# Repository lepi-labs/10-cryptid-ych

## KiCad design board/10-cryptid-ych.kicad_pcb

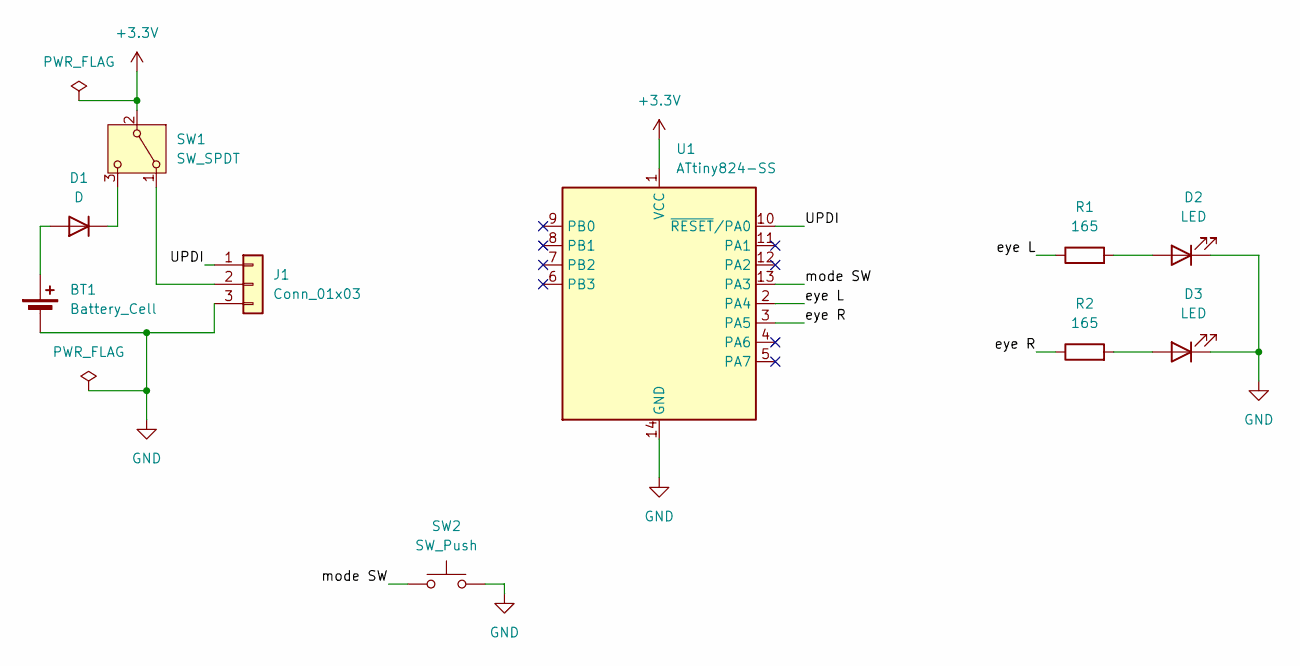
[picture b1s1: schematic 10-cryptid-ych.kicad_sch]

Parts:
BT1: Battery_Cell; BATHLD003SMT
D1: D; D_1206_3216Metric_Pad1.42x1.75mm_HandSolder
D2, D3: LED; LTSTS110KGKT
J1: Conn_01x03; Connector_UPDI_Pad
R1, R2: 165; R_1206_3216Metric_Pad1.30x1.75mm_HandSolder
SW1: SW_SPDT; SWS010020R12SSA
SW2: SW_Push; PHAP3344CR
U1: ATtiny824-SS; SOIC-14_3.9x8.7mm_P1.27mm

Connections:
+3.3V: SW1.2 (B), U1.1 (VCC)
/UPDI: J1.1, U1.10 (~RESET/PA0)
/eye L: R1.1, U1.2 (PA4)
/eye R: R2.1, U1.3 (PA5)
/mode SW: SW2.1, U1.13 (PA3)
GND: BT1.2 (-), D2.1 (K), D3.1 (K), J1.3, SW2.2, U1.14 (GND)
unnamed: BT1.1 (+), D1.2 (A)
unnamed: D1.1 (K), SW1.3 (C)
unnamed: D2.2 (A), R1.2
unnamed: D3.2 (A), R2.2
unnamed: J1.2, SW1.1 (A)

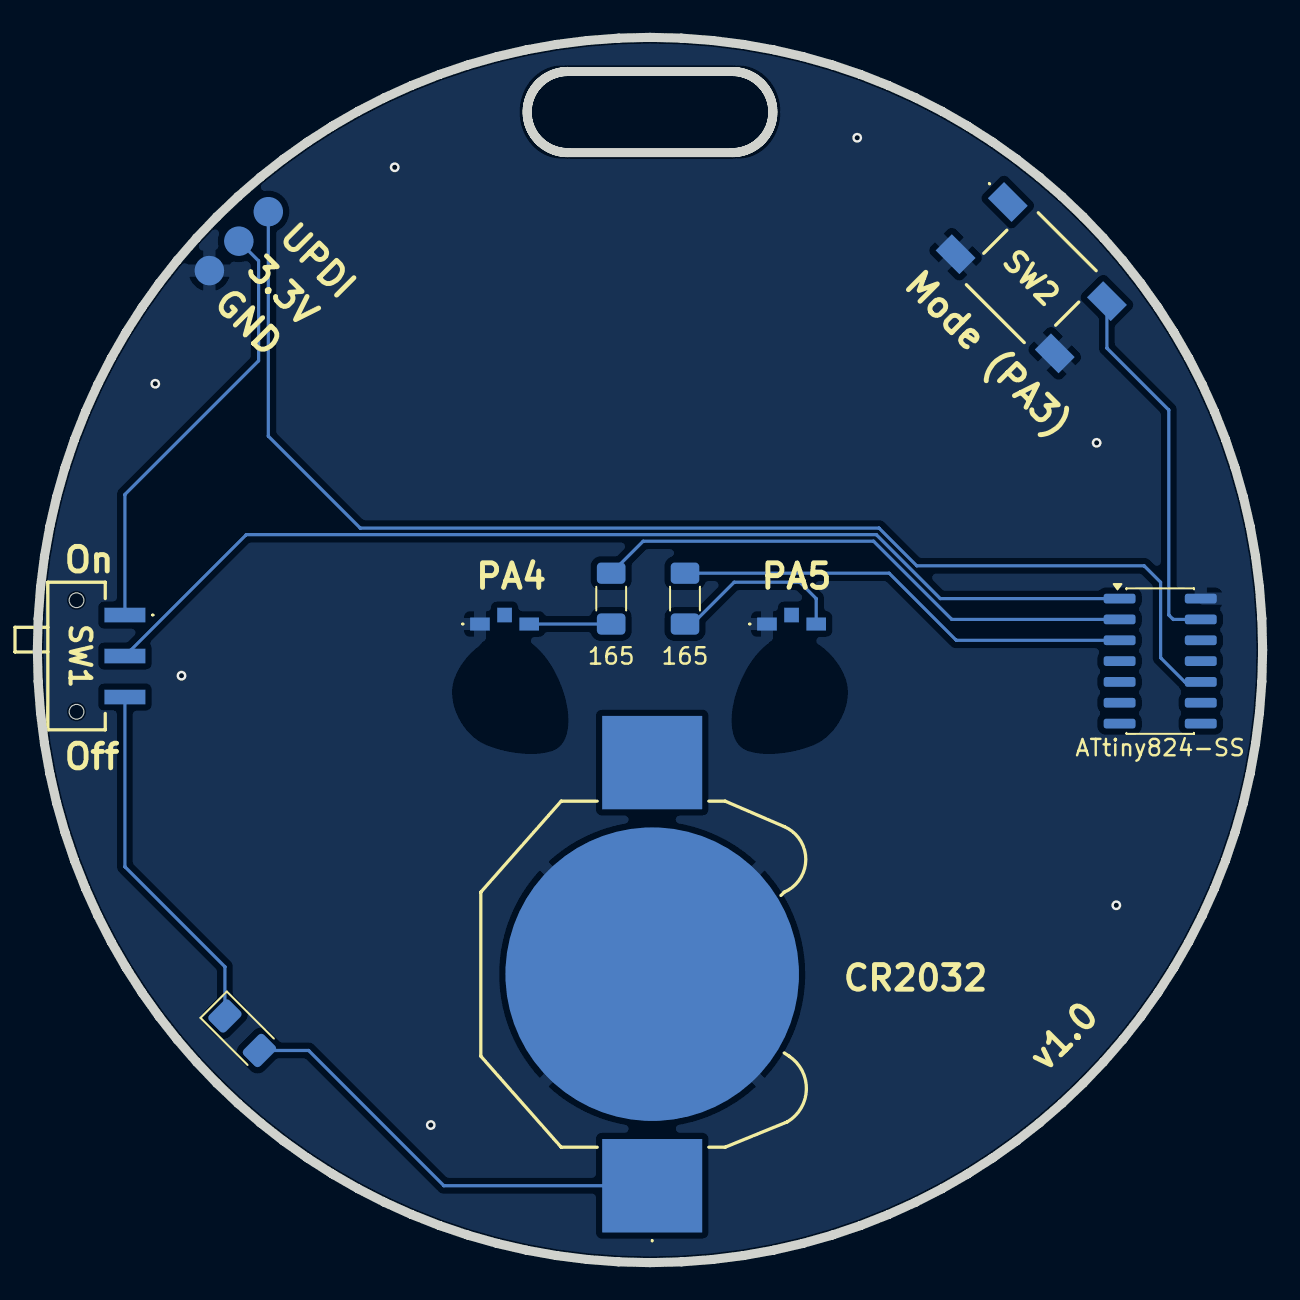
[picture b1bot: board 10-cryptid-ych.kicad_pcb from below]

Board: 2 copper layers, 74.7 x 74.7 mm, 10 parts (10 on the bottom side), 11 nets.
